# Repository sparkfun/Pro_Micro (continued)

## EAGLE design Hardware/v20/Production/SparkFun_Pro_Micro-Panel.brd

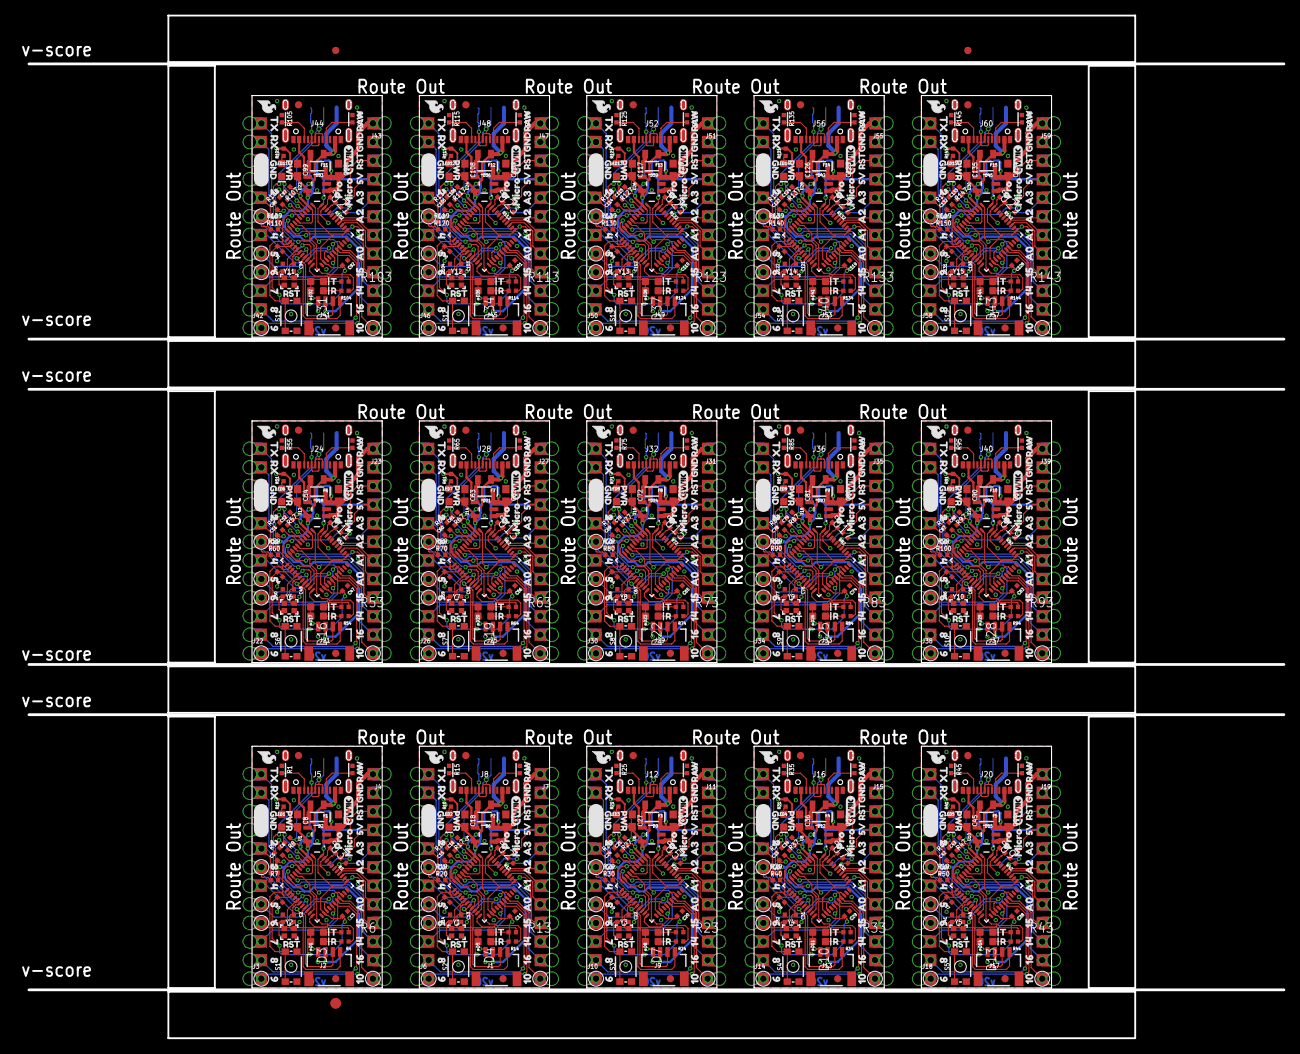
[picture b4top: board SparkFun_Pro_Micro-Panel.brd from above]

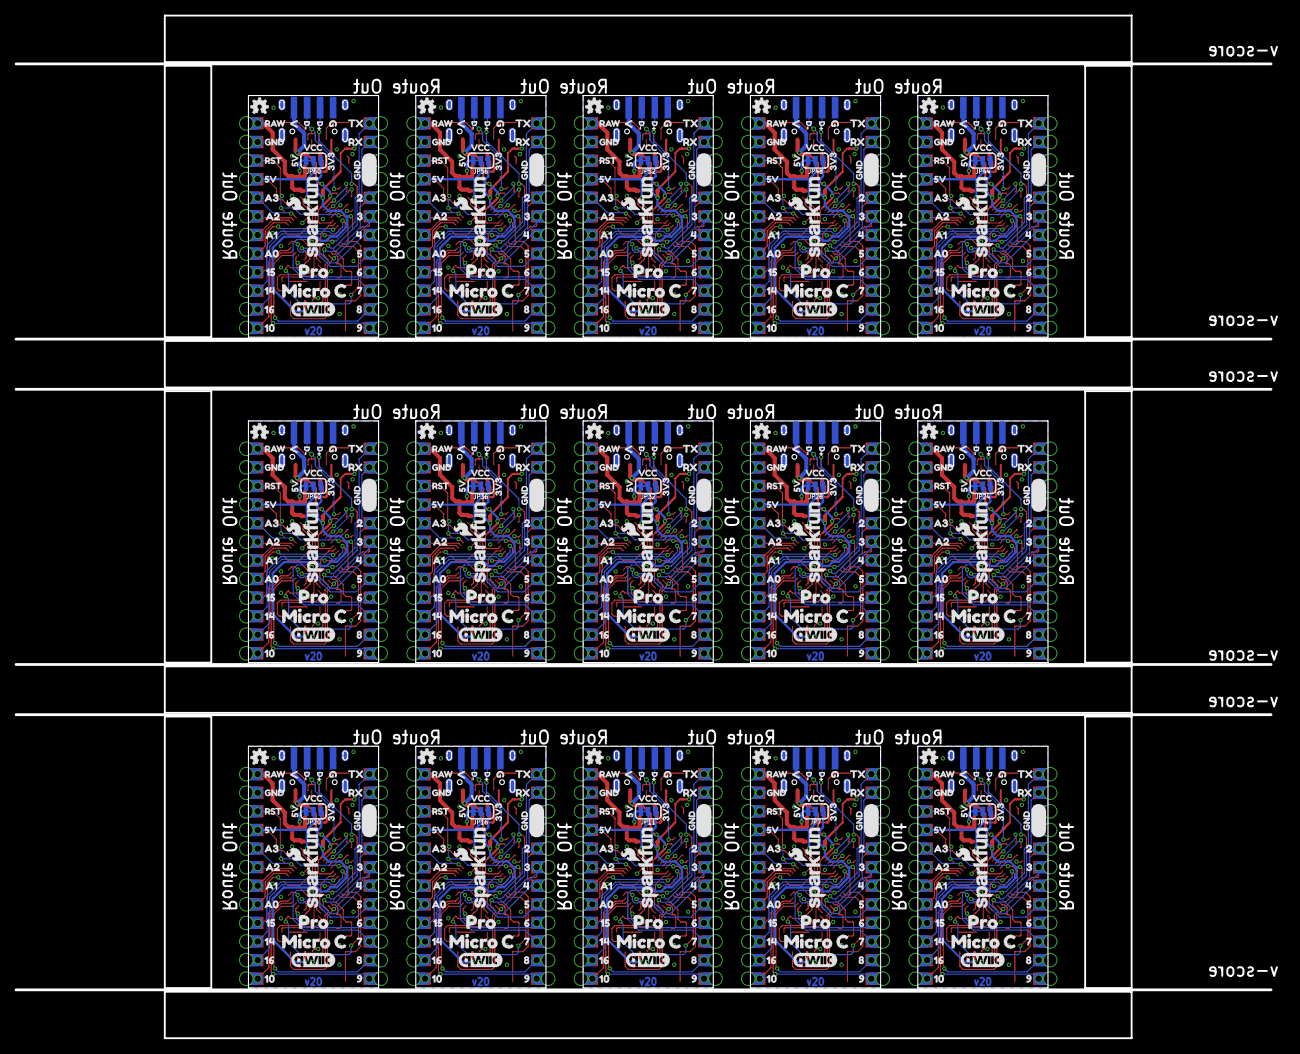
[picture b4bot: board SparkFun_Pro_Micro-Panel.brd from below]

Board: 2 copper layers, 171.4 x 139.7 mm, 1548 parts (570 on the bottom side), 600 nets.

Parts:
C1, C3, C11, C12, C20, C21, C29, C30, C38, C39, C47, C48, C56, C57, C65, C66, C74, C75, C83, C84, C92, C93, C101, C102, C110, C111, C119, C120, C128, C129: 0.1uF; 0402-TIGHT
C2, C4, C13, C14, C22, C23, C31, C32, C40, C41, C49, C50, C58, C59, C67, C68, C76, C77, C85, C86, C94, C95, C103, C104, C112, C113, C121, C122, C130, C131: 22pF; 0402-TIGHT
C5, C6, C9, C10, C15, C16, C19, C24, C25, C28, C33, C34, C37, C42, C43, C46, C51, C52, C55, C60, C61, C64, C69, C70, C73, C78, C79, C82, C87, C88, C91, C96, C97, C100, C105, C106, C109, C114, C115, C118, C123, C124, C127, C132, C133: 1.0uF; 0402-TIGHT
C7, C8, C17, C18, C26, C27, C35, C36, C44, C45, C53, C54, C62, C63, C71, C72, C80, C81, C89, C90, C98, C99, C107, C108, C116, C117, C125, C126, C134, C135: 10uF; 0603
D1, D5, D8, D11, D14, D17, D20, D23, D26, D29, D32, D35, D38, D41, D44: Yellow; LED-0603
D2, D6, D9, D12, D15, D18, D21, D24, D27, D30, D33, D36, D39, D42, D45: 3A/10V/280mV; SOD-323
D3, D4, D7, D10, D13, D16, D19, D22, D25, D28, D31, D34, D37, D40, D43: GREEN; LED-0603
E$1, E$2: FIDUCIAL-1X2
E$3: FIDUCIAL-1.5X3
F1, F2, F3, F4, F5, F6, F7, F8, F9, F10, F11, F12, F13, F14, F15: 6V 0.5A; 0805
J1, J2, J9, J13, J17, J21, J25, J29, J33, J37, J41, J45, J49, J53, J57: Qwiic; JST04_1MM_RA
J3, J4, J6, J7, J10, J11, J14, J15, J18, J19, J22, J23, J26, J27, J30, J31, J34, J35, J38, J39, J42, J43, J46, J47, J50, J51, J54, J55, J58, J59: 1X12_CASTELLATED
J5, J8, J12, J16, J20, J24, J28, J32, J36, J40, J44, J48, J52, J56, J60: USB-C-16P-5
JP1, JP2, JP3, JP5, JP8, JP9, JP12, JP13, JP17, JP18, JP21, JP22, JP25, JP26, JP29, JP30, JP33, JP34, JP37, JP38, JP41, JP42, JP45, JP46, JP49, JP50, JP53, JP54, JP57, JP58: FIDUCIAL1X2; FIDUCIAL-1X2
JP4, JP7, JP11, JP16, JP20, JP24, JP28, JP32, JP36, JP40, JP44, JP48, JP52, JP56, JP60: SMT-JUMPER_3_1-NC_TRACE_SILK
JP6, JP10, JP14, JP15, JP19, JP23, JP27, JP31, JP35, JP39, JP43, JP47, JP51, JP55, JP59: USB_SOLDER_PADS; USB-SOLDER-PADS
LED1, LED2, LED3, LED4, LED5, LED6, LED7, LED8, LED9, LED10, LED11, LED12, LED13, LED14, LED15: RED; LED-0603
LOGO1, LOGO5, LOGO9, LOGO13, LOGO17, LOGO21, LOGO25, LOGO29, LOGO33, LOGO37, LOGO41, LOGO45, LOGO49, LOGO53, LOGO57: SFE_LOGO_NAME_FLAME.1_INCH; SFE_LOGO_NAME_FLAME_.1
LOGO2, LOGO6, LOGO10, LOGO14, LOGO18, LOGO22, LOGO26, LOGO30, LOGO34, LOGO38, LOGO42, LOGO46, LOGO50, LOGO54, LOGO58: QWIIC_LOGO_4MM; QWIIC_4MM
LOGO3, LOGO7, LOGO11, LOGO15, LOGO19, LOGO23, LOGO27, LOGO31, LOGO35, LOGO39, LOGO43, LOGO47, LOGO51, LOGO55, LOGO59: QWIIC_LOGO_6MM; QWIIC_6MM
LOGO4, LOGO8, LOGO12, LOGO16, LOGO20, LOGO24, LOGO28, LOGO32, LOGO36, LOGO40, LOGO44, LOGO48, LOGO52, LOGO56, LOGO60: SFE_LOGO_FLAME.1_INCH; SFE_LOGO_FLAME_.1
R1, R3, R15, R16, R25, R26, R35, R36, R45, R46, R55, R56, R65, R66, R75, R76, R85, R86, R95, R96, R105, R106, R115, R116, R125, R126, R135, R136, R145, R146: 5.1k; 0402-TIGHT
R2, R12, R22, R32, R42, R52, R62, R72, R82, R92, R102, R112, R122, R132, R142: 10k; 0402-TIGHT
R4, R6, R10, R11, R13, R14, R21, R23, R24, R31, R33, R34, R41, R43, R44, R51, R53, R54, R61, R63, R64, R71, R73, R74, R81, R83, R84, R91, R93, R94, R101, R103, R104, R111, R113, R114, R121, R123, R124, R131, R133, R134, R141, R143, R144: 1k; 0402-TIGHT
R5, R7, R19, R20, R29, R30, R39, R40, R49, R50, R59, R60, R69, R70, R79, R80, R89, R90, R99, R100, R109, R110, R119, R120, R129, R130, R139, R140, R149, R150: 2.2k; 0402-TIGHT
R8, R9, R17, R18, R27, R28, R37, R38, R47, R48, R57, R58, R67, R68, R77, R78, R87, R88, R97, R98, R107, R108, R117, R118, R127, R128, R137, R138, R147, R148: 22; 0402-TIGHT
S1, S2, S3, S4, S5, S6, S7, S8, S9, S10, S11, S12, S13, S14, S15: Reset; TACTILE_SWITCH_SMD_4.6X2.8MM
U1, U4, U6, U8, U10, U12, U14, U16, U18, U20, U22, U24, U26, U28, U30: 3.3V; SOT23-5
U2, U3, U5, U7, U9, U11, U13, U15, U17, U19, U21, U23, U25, U27, U29: ATmega32U4; QFN-44-NOPAD_1:1
U$1, U$124, U$187, U$250, U$313, U$376, U$439, U$502, U$565, U$628, U$691, U$754, U$817, U$880, U$943: VCC1
U$2, U$38, U$70, U$101, U$133, U$164, U$196, U$227, U$259, U$290, U$322, U$353, U$385, U$416, U$448, U$479, U$511, U$542, U$574, U$605, U$637, U$668, U$700, U$731, U$763, U$794, U$826, U$857, U$889, U$920: 156
U$3, U$20, U$127, U$190, U$253, U$316, U$379, U$442, U$505, U$568, U$631, U$694, U$757, U$820, U$883: OSHW-LOGOMINI; OSHW-LOGO-MINI
U$4, U$48, U$71, U$103, U$134, U$166, U$197, U$229, U$260, U$292, U$323, U$355, U$386, U$418, U$449, U$481, U$512, U$544, U$575, U$607, U$638, U$670, U$701, U$733, U$764, U$796, U$827, U$859, U$890, U$922: 164
U$5, U$57, U$72, U$112, U$135, U$175, U$198, U$238, U$261, U$301, U$324, U$364, U$387, U$427, U$450, U$490, U$513, U$553, U$576, U$616, U$639, U$679, U$702, U$742, U$765, U$805, U$828, U$868, U$891, U$931: 218
U$6, U$56, U$73, U$111, U$136, U$174, U$199, U$237, U$262, U$300, U$325, U$363, U$388, U$426, U$451, U$489, U$514, U$552, U$577, U$615, U$640, U$678, U$703, U$741, U$766, U$804, U$829, U$867, U$892, U$930: 317
U$7, U$54, U$74, U$109, U$137, U$172, U$200, U$235, U$263, U$298, U$326, U$361, U$389, U$424, U$452, U$487, U$515, U$550, U$578, U$613, U$641, U$676, U$704, U$739, U$767, U$802, U$830, U$865, U$893, U$928: 515
U$8, U$53, U$75, U$108, U$138, U$171, U$201, U$234, U$264, U$297, U$327, U$360, U$390, U$423, U$453, U$486, U$516, U$549, U$579, U$612, U$642, U$675, U$705, U$738, U$768, U$801, U$831, U$864, U$894, U$927: 614
U$9, U$52, U$76, U$107, U$139, U$170, U$202, U$233, U$265, U$296, U$328, U$359, U$391, U$422, U$454, U$485, U$517, U$548, U$580, U$611, U$643, U$674, U$706, U$737, U$769, U$800, U$832, U$863, U$895, U$926: 713
U$10, U$51, U$77, U$106, U$140, U$169, U$203, U$232, U$266, U$295, U$329, U$358, U$392, U$421, U$455, U$484, U$518, U$547, U$581, U$610, U$644, U$673, U$707, U$736, U$770, U$799, U$833, U$862, U$896, U$925: 812
U$11, U$22, U$32, U$58, U$84, U$91, U$113, U$116, U$147, U$154, U$176, U$179, U$210, U$217, U$239, U$242, U$273, U$280, U$302, U$305, U$336, U$343, U$365, U$368, U$399, U$406, U$428, U$431, U$462, U$469, U$491, U$494, U$525, U$532, U$554, U$557, U$588, U$595, U$617, U$620, U$651, U$658, U$680, U$683, U$714, U$721, U$743, U$746, U$777, U$784, U$806, U$809, U$840, U$847, U$869, U$872, U$903, U$910, U$932, U$935: GND4
U$12, U$46, U$88, U$95, U$151, U$158, U$214, U$221, U$277, U$284, U$340, U$347, U$403, U$410, U$466, U$473, U$529, U$536, U$592, U$599, U$655, U$662, U$718, U$725, U$781, U$788, U$844, U$851, U$907, U$914: RAW5
U$13, U$33, U$55, U$110, U$128, U$173, U$191, U$236, U$254, U$299, U$317, U$362, U$380, U$425, U$443, U$488, U$506, U$551, U$569, U$614, U$632, U$677, U$695, U$740, U$758, U$803, U$821, U$866, U$884, U$929: 45
U$14, U$89, U$152, U$215, U$278, U$341, U$404, U$467, U$530, U$593, U$656, U$719, U$782, U$845, U$908: T8
U$15, U$64, U$65, U$123, U$125, U$126, U$186, U$188, U$189, U$249, U$251, U$252, U$312, U$314, U$315, U$375, U$377, U$378, U$438, U$440, U$441, U$501, U$503, U$504, U$564, U$566, U$567, U$627, U$629, U$630, U$690, U$692, U$693, U$753, U$755, U$756, U$816, U$818, U$819, U$879, U$881, U$882, U$942, U$944, U$945: 5V1
U$16, U$50, U$78, U$105, U$141, U$168, U$204, U$231, U$267, U$294, U$330, U$357, U$393, U$420, U$456, U$483, U$519, U$546, U$582, U$609, U$645, U$672, U$708, U$735, U$771, U$798, U$834, U$861, U$897, U$924: 911
U$17, U$37, U$79, U$100, U$142, U$163, U$205, U$226, U$268, U$289, U$331, U$352, U$394, U$415, U$457, U$478, U$520, U$541, U$583, U$604, U$646, U$667, U$709, U$730, U$772, U$793, U$835, U$856, U$898, U$919: A07
U$18, U$60, U$66, U$115, U$129, U$178, U$192, U$241, U$255, U$304, U$318, U$367, U$381, U$430, U$444, U$493, U$507, U$556, U$570, U$619, U$633, U$682, U$696, U$745, U$759, U$808, U$822, U$871, U$885, U$934: TX2
U$19, U$36, U$80, U$99, U$143, U$162, U$206, U$225, U$269, U$288, U$332, U$351, U$395, U$414, U$458, U$477, U$521, U$540, U$584, U$603, U$647, U$666, U$710, U$729, U$773, U$792, U$836, U$855, U$899, U$918: A18
U$21, U$49, U$67, U$104, U$130, U$167, U$193, U$230, U$256, U$293, U$319, U$356, U$382, U$419, U$445, U$482, U$508, U$545, U$571, U$608, U$634, U$671, U$697, U$734, U$760, U$797, U$823, U$860, U$886, U$923: 104
U$23, U$68, U$131, U$194, U$257, U$320, U$383, U$446, U$509, U$572, U$635, U$698, U$761, U$824, U$887: MICRO1
U$24, U$69, U$132, U$195, U$258, U$321, U$384, U$447, U$510, U$573, U$636, U$699, U$762, U$825, U$888: PRO0
U$25, U$31, U$41, U$85, U$90, U$96, U$148, U$153, U$159, U$211, U$216, U$222, U$274, U$279, U$285, U$337, U$342, U$348, U$400, U$405, U$411, U$463, U$468, U$474, U$526, U$531, U$537, U$589, U$594, U$600, U$652, U$657, U$663, U$715, U$720, U$726, U$778, U$783, U$789, U$841, U$846, U$852, U$904, U$909, U$915: RST3
U$26, U$35, U$81, U$98, U$144, U$161, U$207, U$224, U$270, U$287, U$333, U$350, U$396, U$413, U$459, U$476, U$522, U$539, U$585, U$602, U$648, U$665, U$711, U$728, U$774, U$791, U$837, U$854, U$900, U$917: A29
U$27, U$34, U$82, U$97, U$145, U$160, U$208, U$223, U$271, U$286, U$334, U$349, U$397, U$412, U$460, U$475, U$523, U$538, U$586, U$601, U$649, U$664, U$712, U$727, U$775, U$790, U$838, U$853, U$901, U$916: A310
U$28, U$59, U$83, U$114, U$146, U$177, U$209, U$240, U$272, U$303, U$335, U$366, U$398, U$429, U$461, U$492, U$524, U$555, U$587, U$618, U$650, U$681, U$713, U$744, U$776, U$807, U$839, U$870, U$902, U$933: RX20
U$29, U$47, U$86, U$102, U$149, U$165, U$212, U$228, U$275, U$291, U$338, U$354, U$401, U$417, U$464, U$480, U$527, U$543, U$590, U$606, U$653, U$669, U$716, U$732, U$779, U$795, U$842, U$858, U$905, U$921: 145
U$30, U$87, U$150, U$213, U$276, U$339, U$402, U$465, U$528, U$591, U$654, U$717, U$780, U$843, U$906: R9
U$39, U$117, U$180, U$243, U$306, U$369, U$432, U$495, U$558, U$621, U$684, U$747, U$810, U$873, U$936: 3V39
U$40, U$92, U$155, U$218, U$281, U$344, U$407, U$470, U$533, U$596, U$659, U$722, U$785, U$848, U$911: C5
U$42, U$118, U$181, U$244, U$307, U$370, U$433, U$496, U$559, U$622, U$685, U$748, U$811, U$874, U$937: G1
U$43, U$93, U$156, U$219, U$282, U$345, U$408, U$471, U$534, U$597, U$660, U$723, U$786, U$849, U$912: MICRO4
U$44, U$119, U$182, U$245, U$308, U$371, U$434, U$497, U$560, U$623, U$686, U$749, U$812, U$875, U$938: V0
U$45, U$94, U$157, U$220, U$283, U$346, U$409, U$472, U$535, U$598, U$661, U$724, U$787, U$850, U$913: PRO3
U$61, U$120, U$183, U$246, U$309, U$372, U$435, U$498, U$561, U$624, U$687, U$750, U$813, U$876, U$939: D#3
U$62, U$121, U$184, U$247, U$310, U$373, U$436, U$499, U$562, U$625, U$688, U$751, U$814, U$877, U$940: D#4
U$63, U$122, U$185, U$248, U$311, U$374, U$437, U$500, U$563, U$626, U$689, U$752, U$815, U$878, U$941: PWR0
Y1, Y2, Y3, Y4, Y5, Y6, Y7, Y8, Y9, Y10, Y11, Y12, Y13, Y14, Y15: 32MHz; CRYSTAL-SMD-2.0X1.6MM

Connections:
3.3V: C8.2, J2.2, JP4.1, R5.2, R7.2, R11.2, U1.5
3.3V1: C18.2, J1.2, JP7.1, R10.2, R19.2, R20.2, U4.5
3.3V2: C27.2, J9.2, JP11.1, R21.2, R29.2, R30.2, U6.5
3.3V3: C36.2, J13.2, JP16.1, R31.2, R39.2, R40.2, U8.5
3.3V4: C45.2, J17.2, JP20.1, R41.2, R49.2, R50.2, U10.5
3.3V5: C54.2, J21.2, JP24.1, R51.2, R59.2, R60.2, U12.5
3.3V6: C63.2, J25.2, JP28.1, R61.2, R69.2, R70.2, U14.5
3.3V7: C72.2, J29.2, JP32.1, R71.2, R79.2, R80.2, U16.5
3.3V8: C81.2, J33.2, JP36.1, R81.2, R89.2, R90.2, U18.5
3.3V9: C90.2, J37.2, JP40.1, R91.2, R99.2, R100.2, U20.5
3.3V10: C99.2, J41.2, JP44.1, R101.2, R109.2, R110.2, U22.5
3.3V11: C108.2, J45.2, JP48.1, R111.2, R119.2, R120.2, U24.5
3.3V12: C117.2, J49.2, JP52.1, R121.2, R129.2, R130.2, U26.5
3.3V13: C126.2, J53.2, JP56.1, R131.2, R139.2, R140.2, U28.5
3.3V14: C135.2, J57.2, JP60.1, R141.2, R149.2, R150.2, U30.5
A0: J4.8, J4.8B, U3.36
A1: J4.7, J4.7B, U3.37
A2: J4.6, J4.6B, U3.38
A3: J4.5, J4.5B, U3.39
A4: J7.5, J7.5B, U2.39
A5: J7.6, J7.6B, U2.38
A6: J7.7, J7.7B, U2.37
A7: J7.8, J7.8B, U2.36
A8: J11.5, J11.5B, U5.39
A9: J11.6, J11.6B, U5.38
A10: J11.7, J11.7B, U5.37
A11: J11.8, J11.8B, U5.36
A12: J15.5, J15.5B, U7.39
A13: J15.6, J15.6B, U7.38
A14: J15.7, J15.7B, U7.37
A15: J15.8, J15.8B, U7.36
A16: J19.5, J19.5B, U9.39
A17: J19.6, J19.6B, U9.38
A18: J19.7, J19.7B, U9.37
A19: J19.8, J19.8B, U9.36
A20: J23.5, J23.5B, U11.39
A21: J23.6, J23.6B, U11.38
A22: J23.7, J23.7B, U11.37
A23: J23.8, J23.8B, U11.36
A24: J27.5, J27.5B, U13.39
A25: J27.6, J27.6B, U13.38
A26: J27.7, J27.7B, U13.37
A27: J27.8, J27.8B, U13.36
A28: J31.5, J31.5B, U15.39
A29: J31.6, J31.6B, U15.38
A30: J31.7, J31.7B, U15.37
A31: J31.8, J31.8B, U15.36
A32: J35.5, J35.5B, U17.39
A33: J35.6, J35.6B, U17.38
A34: J35.7, J35.7B, U17.37
A35: J35.8, J35.8B, U17.36
A36: J39.5, J39.5B, U19.39
A37: J39.6, J39.6B, U19.38
A38: J39.7, J39.7B, U19.37
A39: J39.8, J39.8B, U19.36
A40: J43.5, J43.5B, U21.39
A41: J43.6, J43.6B, U21.38
A42: J43.7, J43.7B, U21.37
A43: J43.8, J43.8B, U21.36
A44: J47.5, J47.5B, U23.39
A45: J47.6, J47.6B, U23.38
A46: J47.7, J47.7B, U23.37
A47: J47.8, J47.8B, U23.36
A48: J51.5, J51.5B, U25.39
A49: J51.6, J51.6B, U25.38
A50: J51.7, J51.7B, U25.37
A51: J51.8, J51.8B, U25.36
A52: J55.5, J55.5B, U27.39
A53: J55.6, J55.6B, U27.38
A54: J55.7, J55.7B, U27.37
A55: J55.8, J55.8B, U27.36
A56: J59.5, J59.5B, U29.39
A57: J59.6, J59.6B, U29.38
A58: J59.7, J59.7B, U29.37
A59: J59.8, J59.8B, U29.36
AREF: C1.2, U3.42
AREF1: C12.2, U2.42
AREF2: C21.2, U5.42
AREF3: C30.2, U7.42
AREF4: C39.2, U9.42
AREF5: C48.2, U11.42
AREF6: C57.2, U13.42
AREF7: C66.2, U15.42
AREF8: C75.2, U17.42
AREF9: C84.2, U19.42
AREF10: C93.2, U21.42
AREF11: C102.2, U23.42
AREF12: C111.2, U25.42
AREF13: C120.2, U27.42
AREF14: C129.2, U29.42
D1: J6.1, J6.1B, U2.29
D2: J6.2, J6.2B, U2.28
D2/SDA: J2.3, J3.8, J3.8B, R5.1, U3.19
D2/SDA1: J1.3, J6.8, J6.8B, R19.1, U2.19
D2/SDA2: J9.3, J10.8, J10.8B, R29.1, U5.19
D2/SDA3: J13.3, J14.8, J14.8B, R39.1, U7.19
D2/SDA4: J17.3, J18.8, J18.8B, R49.1, U9.19
D2/SDA5: J21.3, J22.8, J22.8B, R59.1, U11.19
D2/SDA6: J25.3, J26.8, J26.8B, R69.1, U13.19
D2/SDA7: J29.3, J30.8, J30.8B, R79.1, U15.19
D2/SDA8: J33.3, J34.8, J34.8B, R89.1, U17.19
D2/SDA9: J37.3, J38.8, J38.8B, R99.1, U19.19
D2/SDA10: J41.3, J42.8, J42.8B, R109.1, U21.19
D2/SDA11: J45.3, J46.8, J46.8B, R119.1, U23.19
D2/SDA12: J49.3, J50.8, J50.8B, R129.1, U25.19
D2/SDA13: J53.3, J54.8, J54.8B, R139.1, U27.19
D2/SDA14: J57.3, J58.8, J58.8B, R149.1, U29.19
D3: J6.6, J6.6B, U2.25
D3/SCL: J2.4, J3.7, J3.7B, R7.1, U3.18
D3/SCL1: J1.4, J6.7, J6.7B, R20.1, U2.18
D3/SCL2: J9.4, J10.7, J10.7B, R30.1, U5.18
D3/SCL3: J13.4, J14.7, J14.7B, R40.1, U7.18
D3/SCL4: J17.4, J18.7, J18.7B, R50.1, U9.18
D3/SCL5: J21.4, J22.7, J22.7B, R60.1, U11.18
D3/SCL6: J25.4, J26.7, J26.7B, R70.1, U13.18
D3/SCL7: J29.4, J30.7, J30.7B, R80.1, U15.18
D3/SCL8: J33.4, J34.7, J34.7B, R90.1, U17.18
D3/SCL9: J37.4, J38.7, J38.7B, R100.1, U19.18
D3/SCL10: J41.4, J42.7, J42.7B, R110.1, U21.18
D3/SCL11: J45.4, J46.7, J46.7B, R120.1, U23.18
D3/SCL12: J49.4, J50.7, J50.7B, R130.1, U25.18
D3/SCL13: J53.4, J54.7, J54.7B, R140.1, U27.18
D3/SCL14: J57.4, J58.7, J58.7B, R150.1, U29.18
D4: J3.6, J3.6B, U3.25
D5: J3.5, J3.5B, U3.31
D6: J3.4, J3.4B, U3.27
D7: J3.3, J3.3B, U3.1
D8: J3.2, J3.2B, U3.28
D9: J3.1, J3.1B, U3.29
D10: J4.12, J4.12B, U3.30
D11: J6.5, J6.5B, U2.31
D12: J6.4, J6.4B, U2.27
D13: J6.3, J6.3B, U2.1
D14: J7.12, J7.12B, U2.30
D15: J10.1, J10.1B, U5.29
D16: J10.2, J10.2B, U5.28
D17: J10.6, J10.6B, U5.25
D18: J10.5, J10.5B, U5.31
D19: J10.4, J10.4B, U5.27
D20: J10.3, J10.3B, U5.1
D21: J11.12, J11.12B, U5.30
D22: J14.1, J14.1B, U7.29
D23: J14.2, J14.2B, U7.28
D24: J14.6, J14.6B, U7.25
D25: J14.5, J14.5B, U7.31
D26: J14.4, J14.4B, U7.27
D27: J14.3, J14.3B, U7.1
D28: J15.12, J15.12B, U7.30
D29: J18.1, J18.1B, U9.29
D30: J18.2, J18.2B, U9.28
D31: J18.6, J18.6B, U9.25
D32: J18.5, J18.5B, U9.31
D33: J18.4, J18.4B, U9.27
D34: J18.3, J18.3B, U9.1
D35: J19.12, J19.12B, U9.30
D36: J22.1, J22.1B, U11.29
D37: J22.2, J22.2B, U11.28
D38: J22.6, J22.6B, U11.25
D39: J22.5, J22.5B, U11.31
D40: J22.4, J22.4B, U11.27
D41: J22.3, J22.3B, U11.1
D42: J23.12, J23.12B, U11.30
D43: J26.1, J26.1B, U13.29
D44: J26.2, J26.2B, U13.28
D45: J26.6, J26.6B, U13.25
D46: J26.5, J26.5B, U13.31
D47: J26.4, J26.4B, U13.27
D48: J26.3, J26.3B, U13.1
D49: J27.12, J27.12B, U13.30
D50: J30.1, J30.1B, U15.29
D51: J30.2, J30.2B, U15.28
D52: J30.6, J30.6B, U15.25
D53: J30.5, J30.5B, U15.31
D54: J30.4, J30.4B, U15.27
D55: J30.3, J30.3B, U15.1
D56: J31.12, J31.12B, U15.30
D57: J34.1, J34.1B, U17.29
D58: J34.2, J34.2B, U17.28
D59: J34.6, J34.6B, U17.25
D60: J34.5, J34.5B, U17.31
D61: J34.4, J34.4B, U17.27
D62: J34.3, J34.3B, U17.1
D63: J35.12, J35.12B, U17.30
D64: J38.1, J38.1B, U19.29
D65: J38.2, J38.2B, U19.28
D66: J38.6, J38.6B, U19.25
D67: J38.5, J38.5B, U19.31
D68: J38.4, J38.4B, U19.27
D69: J38.3, J38.3B, U19.1
D70: J39.12, J39.12B, U19.30
D71: J42.1, J42.1B, U21.29
D72: J42.2, J42.2B, U21.28
D73: J42.6, J42.6B, U21.25
D74: J42.5, J42.5B, U21.31
D75: J42.4, J42.4B, U21.27
D76: J42.3, J42.3B, U21.1
D77: J43.12, J43.12B, U21.30
D78: J46.1, J46.1B, U23.29
D79: J46.2, J46.2B, U23.28
D80: J46.6, J46.6B, U23.25
D81: J46.5, J46.5B, U23.31
D82: J46.4, J46.4B, U23.27
D83: J46.3, J46.3B, U23.1
D84: J47.12, J47.12B, U23.30
D85: J50.1, J50.1B, U25.29
D86: J50.2, J50.2B, U25.28
D87: J50.6, J50.6B, U25.25
D88: J50.5, J50.5B, U25.31
D89: J50.4, J50.4B, U25.27
D90: J50.3, J50.3B, U25.1
D91: J51.12, J51.12B, U25.30
D92: J54.1, J54.1B, U27.29
D93: J54.2, J54.2B, U27.28
D94: J54.6, J54.6B, U27.25
D95: J54.5, J54.5B, U27.31
D96: J54.4, J54.4B, U27.27
D97: J54.3, J54.3B, U27.1
D98: J55.12, J55.12B, U27.30
D99: J58.1, J58.1B, U29.29
D100: J58.2, J58.2B, U29.28
D101: J58.6, J58.6B, U29.25
D102: J58.5, J58.5B, U29.31
D103: J58.4, J58.4B, U29.27
D104: J58.3, J58.3B, U29.1
D105: J59.12, J59.12B, U29.30
D+: R9.2, U3.4
D+1: R18.2, U2.4
D+2: R28.2, U5.4
D+3: R38.2, U7.4
D+4: R48.2, U9.4
D+5: R58.2, U11.4
D+6: R68.2, U13.4
D+7: R78.2, U15.4
D+8: R88.2, U17.4
D+9: R98.2, U19.4
D+10: R108.2, U21.4
D+11: R118.2, U23.4
D+12: R128.2, U25.4
D+13: R138.2, U27.4
D+14: R148.2, U29.4
D-: R8.2, U3.3
D-1: R17.2, U2.3
D-2: R27.2, U5.3
D-3: R37.2, U7.3
D-4: R47.2, U9.3
D-5: R57.2, U11.3
D-6: R67.2, U13.3
D-7: R77.2, U15.3
D-8: R87.2, U17.3
D-9: R97.2, U19.3
D-10: R107.2, U21.3
D-11: R117.2, U23.3
D-12: R127.2, U25.3
D-13: R137.2, U27.3
D-14: R147.2, U29.3
D-_HV: J5.A7, J5.B7, JP14.D-, R8.1
D-_HV1: J8.A7, J8.B7, JP6.D-, R17.1
D-_HV2: J12.A7, J12.B7, JP10.D-, R27.1
D-_HV3: J16.A7, J16.B7, JP15.D-, R37.1
D-_HV4: J20.A7, J20.B7, JP19.D-, R47.1
D-_HV5: J24.A7, J24.B7, JP23.D-, R57.1
D-_HV6: J28.A7, J28.B7, JP27.D-, R67.1
D-_HV7: J32.A7, J32.B7, JP31.D-, R77.1
D-_HV8: J36.A7, J36.B7, JP35.D-, R87.1
D-_HV9: J40.A7, J40.B7, JP39.D-, R97.1
D-_HV10: J44.A7, J44.B7, JP43.D-, R107.1
D-_HV11: J48.A7, J48.B7, JP47.D-, R117.1
D-_HV12: J52.A7, J52.B7, JP51.D-, R127.1
D-_HV13: J56.A7, J56.B7, JP55.D-, R137.1
D-_HV14: J60.A7, J60.B7, JP59.D-, R147.1
DP_HV: J5.A6, J5.B6, JP14.D+, R9.1
DP_HV1: J8.A6, J8.B6, JP6.D+, R18.1
DP_HV2: J12.A6, J12.B6, JP10.D+, R28.1
DP_HV3: J16.A6, J16.B6, JP15.D+, R38.1
DP_HV4: J20.A6, J20.B6, JP19.D+, R48.1
DP_HV5: J24.A6, J24.B6, JP23.D+, R58.1
DP_HV6: J28.A6, J28.B6, JP27.D+, R68.1
DP_HV7: J32.A6, J32.B6, JP31.D+, R78.1
DP_HV8: J36.A6, J36.B6, JP35.D+, R88.1
DP_HV9: J40.A6, J40.B6, JP39.D+, R98.1
DP_HV10: J44.A6, J44.B6, JP43.D+, R108.1
DP_HV11: J48.A6, J48.B6, JP47.D+, R118.1
DP_HV12: J52.A6, J52.B6, JP51.D+, R128.1
DP_HV13: J56.A6, J56.B6, JP55.D+, R138.1
DP_HV14: J60.A6, J60.B6, JP59.D+, R148.1
GND: C1.1, C2.2, C3.1, C4.2, C5.1, C6.1, C7.1, C8.1, C10.1, J2.1, J3.9, J3.9B, J3.10, J3.10B, J4.2, J4.2B, J5.GND, J5.GND2, JP14.GND, LED1.C, R1.1, R3.1, S1.1, S1.2, U1.2, U3.5, U3.15, U3.23, U3.33, U3.35, U3.43
GND1: C9.1, C11.1, C12.1, C13.2, C14.2, C15.1, C16.1, C17.1, C18.1, J1.1, J6.9, J6.9B, J6.10, J6.10B, J7.2, J7.2B, J8.GND, J8.GND2, JP6.GND, LED2.C, R15.1, R16.1, S2.1, S2.2, U2.5, U2.15, U2.23, U2.33, U2.35, U2.43, U4.2
GND2: C19.1, C20.1, C21.1, C22.2, C23.2, C24.1, C25.1, C26.1, C27.1, J9.1, J10.9, J10.9B, J10.10, J10.10B, J11.2, J11.2B, J12.GND, J12.GND2, JP10.GND, LED3.C, R25.1, R26.1, S3.1, S3.2, U5.5, U5.15, U5.23, U5.33, U5.35, U5.43, U6.2
GND3: C28.1, C29.1, C30.1, C31.2, C32.2, C33.1, C34.1, C35.1, C36.1, J13.1, J14.9, J14.9B, J14.10, J14.10B, J15.2, J15.2B, J16.GND, J16.GND2, JP15.GND, LED4.C, R35.1, R36.1, S4.1, S4.2, U7.5, U7.15, U7.23, U7.33, U7.35, U7.43, U8.2
GND4: C37.1, C38.1, C39.1, C40.2, C41.2, C42.1, C43.1, C44.1, C45.1, J17.1, J18.9, J18.9B, J18.10, J18.10B, J19.2, J19.2B, J20.GND, J20.GND2, JP19.GND, LED5.C, R45.1, R46.1, S5.1, S5.2, U9.5, U9.15, U9.23, U9.33, U9.35, U9.43, U10.2
GND5: C46.1, C47.1, C48.1, C49.2, C50.2, C51.1, C52.1, C53.1, C54.1, J21.1, J22.9, J22.9B, J22.10, J22.10B, J23.2, J23.2B, J24.GND, J24.GND2, JP23.GND, LED6.C, R55.1, R56.1, S6.1, S6.2, U11.5, U11.15, U11.23, U11.33, U11.35, U11.43, U12.2
GND6: C55.1, C56.1, C57.1, C58.2, C59.2, C60.1, C61.1, C62.1, C63.1, J25.1, J26.9, J26.9B, J26.10, J26.10B, J27.2, J27.2B, J28.GND, J28.GND2, JP27.GND, LED7.C, R65.1, R66.1, S7.1, S7.2, U13.5, U13.15, U13.23, U13.33, U13.35, U13.43, U14.2
GND7: C64.1, C65.1, C66.1, C67.2, C68.2, C69.1, C70.1, C71.1, C72.1, J29.1, J30.9, J30.9B, J30.10, J30.10B, J31.2, J31.2B, J32.GND, J32.GND2, JP31.GND, LED8.C, R75.1, R76.1, S8.1, S8.2, U15.5, U15.15, U15.23, U15.33, U15.35, U15.43, U16.2
GND8: C73.1, C74.1, C75.1, C76.2, C77.2, C78.1, C79.1, C80.1, C81.1, J33.1, J34.9, J34.9B, J34.10, J34.10B, J35.2, J35.2B, J36.GND, J36.GND2, JP35.GND, LED9.C, R85.1, R86.1, S9.1, S9.2, U17.5, U17.15, U17.23, U17.33, U17.35, U17.43, U18.2
GND9: C82.1, C83.1, C84.1, C85.2, C86.2, C87.1, C88.1, C89.1, C90.1, J37.1, J38.9, J38.9B, J38.10, J38.10B, J39.2, J39.2B, J40.GND, J40.GND2, JP39.GND, LED10.C, R95.1, R96.1, S10.1, S10.2, U19.5, U19.15, U19.23, U19.33, U19.35, U19.43, U20.2
GND10: C91.1, C92.1, C93.1, C94.2, C95.2, C96.1, C97.1, C98.1, C99.1, J41.1, J42.9, J42.9B, J42.10, J42.10B, J43.2, J43.2B, J44.GND, J44.GND2, JP43.GND, LED11.C, R105.1, R106.1, S11.1, S11.2, U21.5, U21.15, U21.23, U21.33, U21.35, U21.43, U22.2
GND11: C100.1, C101.1, C102.1, C103.2, C104.2, C105.1, C106.1, C107.1, C108.1, J45.1, J46.9, J46.9B, J46.10, J46.10B, J47.2, J47.2B, J48.GND, J48.GND2, JP47.GND, LED12.C, R115.1, R116.1, S12.1, S12.2, U23.5, U23.15, U23.23, U23.33, U23.35, U23.43, U24.2
GND12: C109.1, C110.1, C111.1, C112.2, C113.2, C114.1, C115.1, C116.1, C117.1, J49.1, J50.9, J50.9B, J50.10, J50.10B, J51.2, J51.2B, J52.GND, J52.GND2, JP51.GND, LED13.C, R125.1, R126.1, S13.1, S13.2, U25.5, U25.15, U25.23, U25.33, U25.35, U25.43, U26.2
GND13: C118.1, C119.1, C120.1, C121.2, C122.2, C123.1, C124.1, C125.1, C126.1, J53.1, J54.9, J54.9B, J54.10, J54.10B, J55.2, J55.2B, J56.GND, J56.GND2, JP55.GND, LED14.C, R135.1, R136.1, S14.1, S14.2, U27.5, U27.15, U27.23, U27.33, U27.35, U27.43, U28.2
GND14: C127.1, C128.1, C129.1, C130.2, C131.2, C132.1, C133.1, C134.1, C135.1, J57.1, J58.9, J58.9B, J58.10, J58.10B, J59.2, J59.2B, J60.GND, J60.GND2, JP59.GND, LED15.C, R145.1, R146.1, S15.1, S15.2, U29.5, U29.15, U29.23, U29.33, U29.35, U29.43, U30.2
MISO: J4.10, J4.10B, U3.11
MISO1: J7.10, J7.10B, U2.11
MISO2: J11.10, J11.10B, U5.11
MISO3: J15.10, J15.10B, U7.11
MISO4: J19.10, J19.10B, U9.11
MISO5: J23.10, J23.10B, U11.11
MISO6: J27.10, J27.10B, U13.11
MISO7: J31.10, J31.10B, U15.11
MISO8: J35.10, J35.10B, U17.11
MISO9: J39.10, J39.10B, U19.11
MISO10: J43.10, J43.10B, U21.11
MISO11: J47.10, J47.10B, U23.11
MISO12: J51.10, J51.10B, U25.11
MISO13: J55.10, J55.10B, U27.11
MISO14: J59.10, J59.10B, U29.11
MOSI: J4.11, J4.11B, U3.10
MOSI1: J7.11, J7.11B, U2.10
MOSI2: J11.11, J11.11B, U5.10
MOSI3: J15.11, J15.11B, U7.10
MOSI4: J19.11, J19.11B, U9.10
MOSI5: J23.11, J23.11B, U11.10
MOSI6: J27.11, J27.11B, U13.10
MOSI7: J31.11, J31.11B, U15.10
MOSI8: J35.11, J35.11B, U17.10
MOSI9: J39.11, J39.11B, U19.10
MOSI10: J43.11, J43.11B, U21.10
MOSI11: J47.11, J47.11B, U23.10
MOSI12: J51.11, J51.11B, U25.10
MOSI13: J55.11, J55.11B, U27.10
MOSI14: J59.11, J59.11B, U29.10
unnamed: C4.1, U3.16, Y2.1
unnamed: C2.1, U3.17, Y2.3
unnamed: LED2.A, R10.1
unnamed: C14.1, U2.16, Y1.1
unnamed: D1.C, R4.2
unnamed: C13.1, U2.17, Y1.3
unnamed: D3.C, R6.2
unnamed: D5.C, R14.2
unnamed: J5.A5, R3.2
unnamed: J5.B5, R1.2
unnamed: D4.C, R13.2
unnamed: J8.A5, R16.2
unnamed: J8.B5, R15.2
unnamed: LED3.A, R21.1
unnamed: C23.1, U5.16, Y3.1
unnamed: C22.1, U5.17, Y3.3
unnamed: D8.C, R24.2
unnamed: D7.C, R23.2
unnamed: J12.A5, R26.2
unnamed: J12.B5, R25.2
unnamed: LED4.A, R31.1
unnamed: C32.1, U7.16, Y4.1
unnamed: C31.1, U7.17, Y4.3
unnamed: D11.C, R34.2
unnamed: D10.C, R33.2
unnamed: J16.A5, R36.2
unnamed: J16.B5, R35.2
unnamed: LED5.A, R41.1
unnamed: C41.1, U9.16, Y5.1
unnamed: C40.1, U9.17, Y5.3
unnamed: D14.C, R44.2
unnamed: D13.C, R43.2
unnamed: J20.A5, R46.2
unnamed: J20.B5, R45.2
unnamed: LED6.A, R51.1
unnamed: C50.1, U11.16, Y6.1
unnamed: C49.1, U11.17, Y6.3
unnamed: LED1.A, R11.1
unnamed: D17.C, R54.2
unnamed: D16.C, R53.2
unnamed: J24.A5, R56.2
unnamed: J24.B5, R55.2
unnamed: LED7.A, R61.1
unnamed: C59.1, U13.16, Y7.1
unnamed: C58.1, U13.17, Y7.3
unnamed: D20.C, R64.2
unnamed: D19.C, R63.2
unnamed: J28.A5, R66.2
unnamed: J28.B5, R65.2
unnamed: LED8.A, R71.1
unnamed: C68.1, U15.16, Y8.1
unnamed: C67.1, U15.17, Y8.3
unnamed: D23.C, R74.2
unnamed: D22.C, R73.2
unnamed: J32.A5, R76.2
unnamed: J32.B5, R75.2
unnamed: LED9.A, R81.1
unnamed: C77.1, U17.16, Y9.1
unnamed: C76.1, U17.17, Y9.3
unnamed: D26.C, R84.2
unnamed: D25.C, R83.2
unnamed: J36.A5, R86.2
unnamed: J36.B5, R85.2
unnamed: LED10.A, R91.1
unnamed: C86.1, U19.16, Y10.1
unnamed: C85.1, U19.17, Y10.3
unnamed: D29.C, R94.2
unnamed: D28.C, R93.2
unnamed: J40.A5, R96.2
unnamed: J40.B5, R95.2
unnamed: LED11.A, R101.1
unnamed: C95.1, U21.16, Y11.1
unnamed: C94.1, U21.17, Y11.3
unnamed: D32.C, R104.2
unnamed: D31.C, R103.2
unnamed: J44.A5, R106.2
unnamed: J44.B5, R105.2
unnamed: LED12.A, R111.1
unnamed: C104.1, U23.16, Y12.1
unnamed: C103.1, U23.17, Y12.3
unnamed: D35.C, R114.2
unnamed: D34.C, R113.2
unnamed: J48.A5, R116.2
unnamed: J48.B5, R115.2
unnamed: LED13.A, R121.1
unnamed: C113.1, U25.16, Y13.1
unnamed: C112.1, U25.17, Y13.3
unnamed: D38.C, R124.2
unnamed: D37.C, R123.2
unnamed: J52.A5, R126.2
unnamed: J52.B5, R125.2
unnamed: LED14.A, R131.1
unnamed: C122.1, U27.16, Y14.1
unnamed: C121.1, U27.17, Y14.3
unnamed: D41.C, R134.2
unnamed: D40.C, R133.2
unnamed: J56.A5, R136.2
unnamed: J56.B5, R135.2
unnamed: LED15.A, R141.1
unnamed: C131.1, U29.16, Y15.1
unnamed: C130.1, U29.17, Y15.3
unnamed: D44.C, R144.2
unnamed: D43.C, R143.2
unnamed: J60.A5, R146.2
unnamed: J60.B5, R145.2
RAW: C7.2, D2.C, J4.1, J4.1B, JP4.3, U1.1, U1.3
RAW1: C17.2, D6.C, J7.1, J7.1B, JP7.3, U4.1, U4.3
RAW2: C26.2, D9.C, J11.1, J11.1B, JP11.3, U6.1, U6.3
RAW3: C35.2, D12.C, J15.1, J15.1B, JP16.3, U8.1, U8.3
RAW4: C44.2, D15.C, J19.1, J19.1B, JP20.3, U10.1, U10.3
RAW5: C53.2, D18.C, J23.1, J23.1B, JP24.3, U12.1, U12.3
RAW6: C62.2, D21.C, J27.1, J27.1B, JP28.3, U14.1, U14.3
RAW7: C71.2, D24.C, J31.1, J31.1B, JP32.3, U16.1, U16.3
RAW8: C80.2, D27.C, J35.1, J35.1B, JP36.3, U18.1, U18.3
RAW9: C89.2, D30.C, J39.1, J39.1B, JP40.3, U20.1, U20.3
RAW10: C98.2, D33.C, J43.1, J43.1B, JP44.3, U22.1, U22.3
RAW11: C107.2, D36.C, J47.1, J47.1B, JP48.3, U24.1, U24.3
RAW12: C116.2, D39.C, J51.1, J51.1B, JP52.3, U26.1, U26.3
RAW13: C125.2, D42.C, J55.1, J55.1B, JP56.3, U28.1, U28.3
RAW14: C134.2, D45.C, J59.1, J59.1B, JP60.3, U30.1, U30.3
RESET: J4.3, J4.3B, R2.1, S1.3, S1.4, U3.13
RESET1: J7.3, J7.3B, R12.1, S2.3, S2.4, U2.13
RESET2: J11.3, J11.3B, R22.1, S3.3, S3.4, U5.13
RESET3: J15.3, J15.3B, R32.1, S4.3, S4.4, U7.13
RESET4: J19.3, J19.3B, R42.1, S5.3, S5.4, U9.13
RESET5: J23.3, J23.3B, R52.1, S6.3, S6.4, U11.13
RESET6: J27.3, J27.3B, R62.1, S7.3, S7.4, U13.13
RESET7: J31.3, J31.3B, R72.1, S8.3, S8.4, U15.13
RESET8: J35.3, J35.3B, R82.1, S9.3, S9.4, U17.13
RESET9: J39.3, J39.3B, R92.1, S10.3, S10.4, U19.13
RESET10: J43.3, J43.3B, R102.1, S11.3, S11.4, U21.13
RESET11: J47.3, J47.3B, R112.1, S12.3, S12.4, U23.13
RESET12: J51.3, J51.3B, R122.1, S13.3, S13.4, U25.13
RESET13: J55.3, J55.3B, R132.1, S14.3, S14.4, U27.13
RESET14: J59.3, J59.3B, R142.1, S15.3, S15.4, U29.13
RXI: J3.11, J3.11B, U3.20
RXI1: J6.11, J6.11B, U2.20
RXI2: J10.11, J10.11B, U5.20
RXI3: J14.11, J14.11B, U7.20
RXI4: J18.11, J18.11B, U9.20
RXI5: J22.11, J22.11B, U11.20
RXI6: J26.11, J26.11B, U13.20
RXI7: J30.11, J30.11B, U15.20
RXI8: J34.11, J34.11B, U17.20
RXI9: J38.11, J38.11B, U19.20
RXI10: J42.11, J42.11B, U21.20
RXI11: J46.11, J46.11B, U23.20
RXI12: J50.11, J50.11B, U25.20
RXI13: J54.11, J54.11B, U27.20
RXI14: J58.11, J58.11B, U29.20
RXLED: R4.1, U3.8
RXLED1: R14.1, U2.8
RXLED2: R24.1, U5.8
RXLED3: R34.1, U7.8
RXLED4: R44.1, U9.8
RXLED5: R54.1, U11.8
RXLED6: R64.1, U13.8
RXLED7: R74.1, U15.8
RXLED8: R84.1, U17.8
RXLED9: R94.1, U19.8
RXLED10: R104.1, U21.8
RXLED11: R114.1, U23.8
RXLED12: R124.1, U25.8
RXLED13: R134.1, U27.8
RXLED14: R144.1, U29.8
SCK: J4.9, J4.9B, U3.9
SCK1: J7.9, J7.9B, U2.9
SCK2: J11.9, J11.9B, U5.9
SCK3: J15.9, J15.9B, U7.9
SCK4: J19.9, J19.9B, U9.9
SCK5: J23.9, J23.9B, U11.9
SCK6: J27.9, J27.9B, U13.9
SCK7: J31.9, J31.9B, U15.9
SCK8: J35.9, J35.9B, U17.9
SCK9: J39.9, J39.9B, U19.9
SCK10: J43.9, J43.9B, U21.9
SCK11: J47.9, J47.9B, U23.9
SCK12: J51.9, J51.9B, U25.9
SCK13: J55.9, J55.9B, U27.9
SCK14: J59.9, J59.9B, U29.9
TXLED: R6.1, U3.22
TXLED1: R13.1, U2.22
TXLED2: R23.1, U5.22
TXLED3: R33.1, U7.22
TXLED4: R43.1, U9.22
TXLED5: R53.1, U11.22
TXLED6: R63.1, U13.22
TXLED7: R73.1, U15.22
TXLED8: R83.1, U17.22
TXLED9: R93.1, U19.22
TXLED10: R103.1, U21.22
TXLED11: R113.1, U23.22
TXLED12: R123.1, U25.22
TXLED13: R133.1, U27.22
TXLED14: R143.1, U29.22
TXO: J3.12, J3.12B, U3.21
TXO1: J6.12, J6.12B, U2.21
TXO2: J10.12, J10.12B, U5.21
TXO3: J14.12, J14.12B, U7.21
TXO4: J18.12, J18.12B, U9.21
TXO5: J22.12, J22.12B, U11.21
TXO6: J26.12, J26.12B, U13.21
TXO7: J30.12, J30.12B, U15.21
TXO8: J34.12, J34.12B, U17.21
TXO9: J38.12, J38.12B, U19.21
TXO10: J42.12, J42.12B, U21.21
TXO11: J46.12, J46.12B, U23.21
TXO12: J50.12, J50.12B, U25.21
TXO13: J54.12, J54.12B, U27.21
TXO14: J58.12, J58.12B, U29.21
UCAP: C5.2, U3.6
UCAP1: C15.2, U2.6
UCAP2: C24.2, U5.6
UCAP3: C33.2, U7.6
UCAP4: C42.2, U9.6
UCAP5: C51.2, U11.6
UCAP6: C60.2, U13.6
UCAP7: C69.2, U15.6
UCAP8: C78.2, U17.6
UCAP9: C87.2, U19.6
UCAP10: C96.2, U21.6
UCAP11: C105.2, U23.6
UCAP12: C114.2, U25.6
UCAP13: C123.2, U27.6
UCAP14: C132.2, U29.6
USB_RAW: D2.A, F1.2
USB_RAW1: D6.A, F2.2
USB_RAW2: D9.A, F3.2
USB_RAW3: D12.A, F4.2
USB_RAW4: D15.A, F5.2
USB_RAW5: D18.A, F6.2
USB_RAW6: D21.A, F7.2
USB_RAW7: D24.A, F8.2
USB_RAW8: D27.A, F9.2
USB_RAW9: D30.A, F10.2
USB_RAW10: D33.A, F11.2
USB_RAW11: D36.A, F12.2
USB_RAW12: D39.A, F13.2
USB_RAW13: D42.A, F14.2
USB_RAW14: D45.A, F15.2
VCC: C3.2, C10.2, D1.A, D3.A, J4.4, J4.4B, JP4.2, R2.2, U3.14, U3.24, U3.34, U3.44
VCC1: C9.2, C11.2, D4.A, D5.A, J7.4, J7.4B, JP7.2, R12.2, U2.14, U2.24, U2.34, U2.44
VCC2: C19.2, C20.2, D7.A, D8.A, J11.4, J11.4B, JP11.2, R22.2, U5.14, U5.24, U5.34, U5.44
VCC3: C28.2, C29.2, D10.A, D11.A, J15.4, J15.4B, JP16.2, R32.2, U7.14, U7.24, U7.34, U7.44
VCC4: C37.2, C38.2, D13.A, D14.A, J19.4, J19.4B, JP20.2, R42.2, U9.14, U9.24, U9.34, U9.44
VCC5: C46.2, C47.2, D16.A, D17.A, J23.4, J23.4B, JP24.2, R52.2, U11.14, U11.24, U11.34, U11.44
VCC6: C55.2, C56.2, D19.A, D20.A, J27.4, J27.4B, JP28.2, R62.2, U13.14, U13.24, U13.34, U13.44
VCC7: C64.2, C65.2, D22.A, D23.A, J31.4, J31.4B, JP32.2, R72.2, U15.14, U15.24, U15.34, U15.44
VCC8: C73.2, C74.2, D25.A, D26.A, J35.4, J35.4B, JP36.2, R82.2, U17.14, U17.24, U17.34, U17.44
VCC9: C82.2, C83.2, D28.A, D29.A, J39.4, J39.4B, JP40.2, R92.2, U19.14, U19.24, U19.34, U19.44
VCC10: C91.2, C92.2, D31.A, D32.A, J43.4, J43.4B, JP44.2, R102.2, U21.14, U21.24, U21.34, U21.44
VCC11: C100.2, C101.2, D34.A, D35.A, J47.4, J47.4B, JP48.2, R112.2, U23.14, U23.24, U23.34, U23.44
VCC12: C109.2, C110.2, D37.A, D38.A, J51.4, J51.4B, JP52.2, R122.2, U25.14, U25.24, U25.34, U25.44
VCC13: C118.2, C119.2, D40.A, D41.A, J55.4, J55.4B, JP56.2, R132.2, U27.14, U27.24, U27.34, U27.44
VCC14: C127.2, C128.2, D43.A, D44.A, J59.4, J59.4B, JP60.2, R142.2, U29.14, U29.24, U29.34, U29.44
V_USB: C6.2, F1.1, J5.VBUS1, J5.VBUS2, JP14.VBUS, U3.2, U3.7
V_USB1: C16.2, F2.1, J8.VBUS1, J8.VBUS2, JP6.VBUS, U2.2, U2.7
V_USB2: C25.2, F3.1, J12.VBUS1, J12.VBUS2, JP10.VBUS, U5.2, U5.7
V_USB3: C34.2, F4.1, J16.VBUS1, J16.VBUS2, JP15.VBUS, U7.2, U7.7
V_USB4: C43.2, F5.1, J20.VBUS1, J20.VBUS2, JP19.VBUS, U9.2, U9.7
V_USB5: C52.2, F6.1, J24.VBUS1, J24.VBUS2, JP23.VBUS, U11.2, U11.7
V_USB6: C61.2, F7.1, J28.VBUS1, J28.VBUS2, JP27.VBUS, U13.2, U13.7
V_USB7: C70.2, F8.1, J32.VBUS1, J32.VBUS2, JP31.VBUS, U15.2, U15.7
V_USB8: C79.2, F9.1, J36.VBUS1, J36.VBUS2, JP35.VBUS, U17.2, U17.7
V_USB9: C88.2, F10.1, J40.VBUS1, J40.VBUS2, JP39.VBUS, U19.2, U19.7
V_USB10: C97.2, F11.1, J44.VBUS1, J44.VBUS2, JP43.VBUS, U21.2, U21.7
V_USB11: C106.2, F12.1, J48.VBUS1, J48.VBUS2, JP47.VBUS, U23.2, U23.7
V_USB12: C115.2, F13.1, J52.VBUS1, J52.VBUS2, JP51.VBUS, U25.2, U25.7
V_USB13: C124.2, F14.1, J56.VBUS1, J56.VBUS2, JP55.VBUS, U27.2, U27.7
V_USB14: C133.2, F15.1, J60.VBUS1, J60.VBUS2, JP59.VBUS, U29.2, U29.7

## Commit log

2013-05-28 Adding hardware files for revision v13
    Ready for prototype
    -Updated QFN Package on 32U4 to be 1:1
    -Updated Symbol of 32U4 in Schematic (switched MISO and SS placement)
    -Renamed SS net to D14 (from D17)
    -Re-Routed directly inward or outward from each leg on the IC
    -Added two small squares of tRestrict to keep the ground plane away from
2013-10-18 Updated v13 design files
    Updated usb connector, IC footprint and route job and moved from 0402 to
    0603.
2014-08-07 Updating README, adding gitignore files
2015-06-19 Updating file names
2015-06-19 Fixing 32u4 pin names
2015-10-13 Adding Pro Micro datasheets
2017-01-31 Adding graphical datasheet fixes from Michelle
2018-01-29 Wrong Pin in Graphical Datasheet
    Mark and a customer noticed that the TX_LED pin is mislabeled on the Graphical Datasheets for the Pro Micro [ [https://github.com/sparkfun/SF32u4_boards/blob/master/sparkfun/avr/variants/promicro/pin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
2018-01-29 Create LICENSE.md
    Add License
2018-01-29 Update README.md
    -Add links to both versions of Pro Micro
    -Add link to hookup guide
    -Add links to Board Addon
    -Add link to graphical datasheets githip repo
2018-01-29 Create Blinkies.ino
    Add example code from tutorial
2018-01-29 Create SimpleKeyboard_HID.ino
    Add example code for keyboard from hookup guide
2018-01-29 Create SimpleJoystickMouse_HID.ino
    Add example code from hookup guide
2018-01-29 Update SimpleKeyboard_HID.ino
    add description
2019-10-09 Proto finished. Add ignore.
2019-10-09 Rev to USB C
2019-10-10 Commit before ordering v20
2019-10-17 Adding production panel, pro micro FP test brd, and castellated test lbr.
2019-11-08 Updates to Pro Micro and Frank
    "Castellated" library '1x12CASTELLATED' and 'PRO_MICRO_C' footprints updated and 'PRO_MICRO_C' device updated.
    Pro Micro C got uniform drill/ring sizing + added plated holes to outside in place of drills
    Frank got 1U Keycap standard switch spacing and updated Pro Micro footprint.
2019-11-08 Red boards ordered
    Modify castellated 1x12 to larger diameter plated castellated holes. Panelize with route-out around castellated edges. Scoot Qwiic connector in to use that side of the board as the tab.
2019-11-19 Udpate xtal to 16MHz
2019-12-11 Correct prodID on 22 ohm resistors.
2019-12-20 Update SparkFun_Pro_Micro.brd
    - Adding board dimensions
    - Add additional distance between connectors to edge of board
2019-12-20 Update SparkFun_Pro_Micro.brd
    -Add distance USB C connector off edge of board
2020-01-07 fixing paste issue
2020-01-07 Remove old test files
2020-01-07 Update README.md
    update links and description for the Qwiic Pro Micro version
2020-02-06 Add Graphical Datasheets
2020-02-11 changing PROD_ID on series D+/D- resistor to proper PROD_ID
2020-02-12 Update Pro Micro Examples
    - rename files to match the examples in the tutorial
    - adjust the output for the hardware UART in **Example_1_Blinkies_Hello.ino** file to distinguish betweeh the serial monitor
    - add `Keyboard.begin()` in `setup()` for **Example_2a_SimpleKeyboard_HID.ino** (this appears to work without initializing it but it was added to be consistent with Arduino's reference example)
    - add `Mouse.begin()` in `setup()` to **Example_2b_SimpleJoystickMouse_HID.ino** (this appears to work without initializing it but it was added to be consistent with Arduino's reference example)
    - include the ability to invert the mouse using the joystick depending on the orientation of the joystick
2020-02-12 Adjust File name
    - Remove redundant .ino from folder and file name
2020-02-12 Update Old Pro Micro Examples
    - adjust the output for the hardware UART in **Blinkies.ino** file to distinguish betweeh the serial monitor
    - add `Keyboard.begin()` in `setup()` for **SimpleKeyboard_HID.ino** (this appears to work without initializing it but it was added to be consistent with Arduino's reference example)
    - add `Mouse.begin()` in `setup()` to **SimpleJoystickMouse_HID.ino** (this appears to work without initializing it but it was added to be consistent with Arduino's reference example)
    - include the ability to invert the mouse using the joystick depending on the orientation of the joystick
    -autoformat
2020-05-26 Boogie Board Silk Added
2020-05-26 Update SparkFun_Pro_Micro.brd
    Updated ordering instructions
2022-01-11 Resolving firmware conflicts
2022-01-11 Adding new firmware examples
2022-06-16 Add Older Version to Repo
    The product pages for the Pro Micro and the Qwiic Pro Micro USB-C versions currently point to this repo without the older Pro Micro's Hardware Files. Since we are still selling both, I am adding the 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
2024-08-15 updated red LED
    -Updated to new red LED and 4.7K bias resistor
    -Note, this PCB is shared with a 3.3V and 5V version of the pro micro
    -added a table to the schematic to inform production.
